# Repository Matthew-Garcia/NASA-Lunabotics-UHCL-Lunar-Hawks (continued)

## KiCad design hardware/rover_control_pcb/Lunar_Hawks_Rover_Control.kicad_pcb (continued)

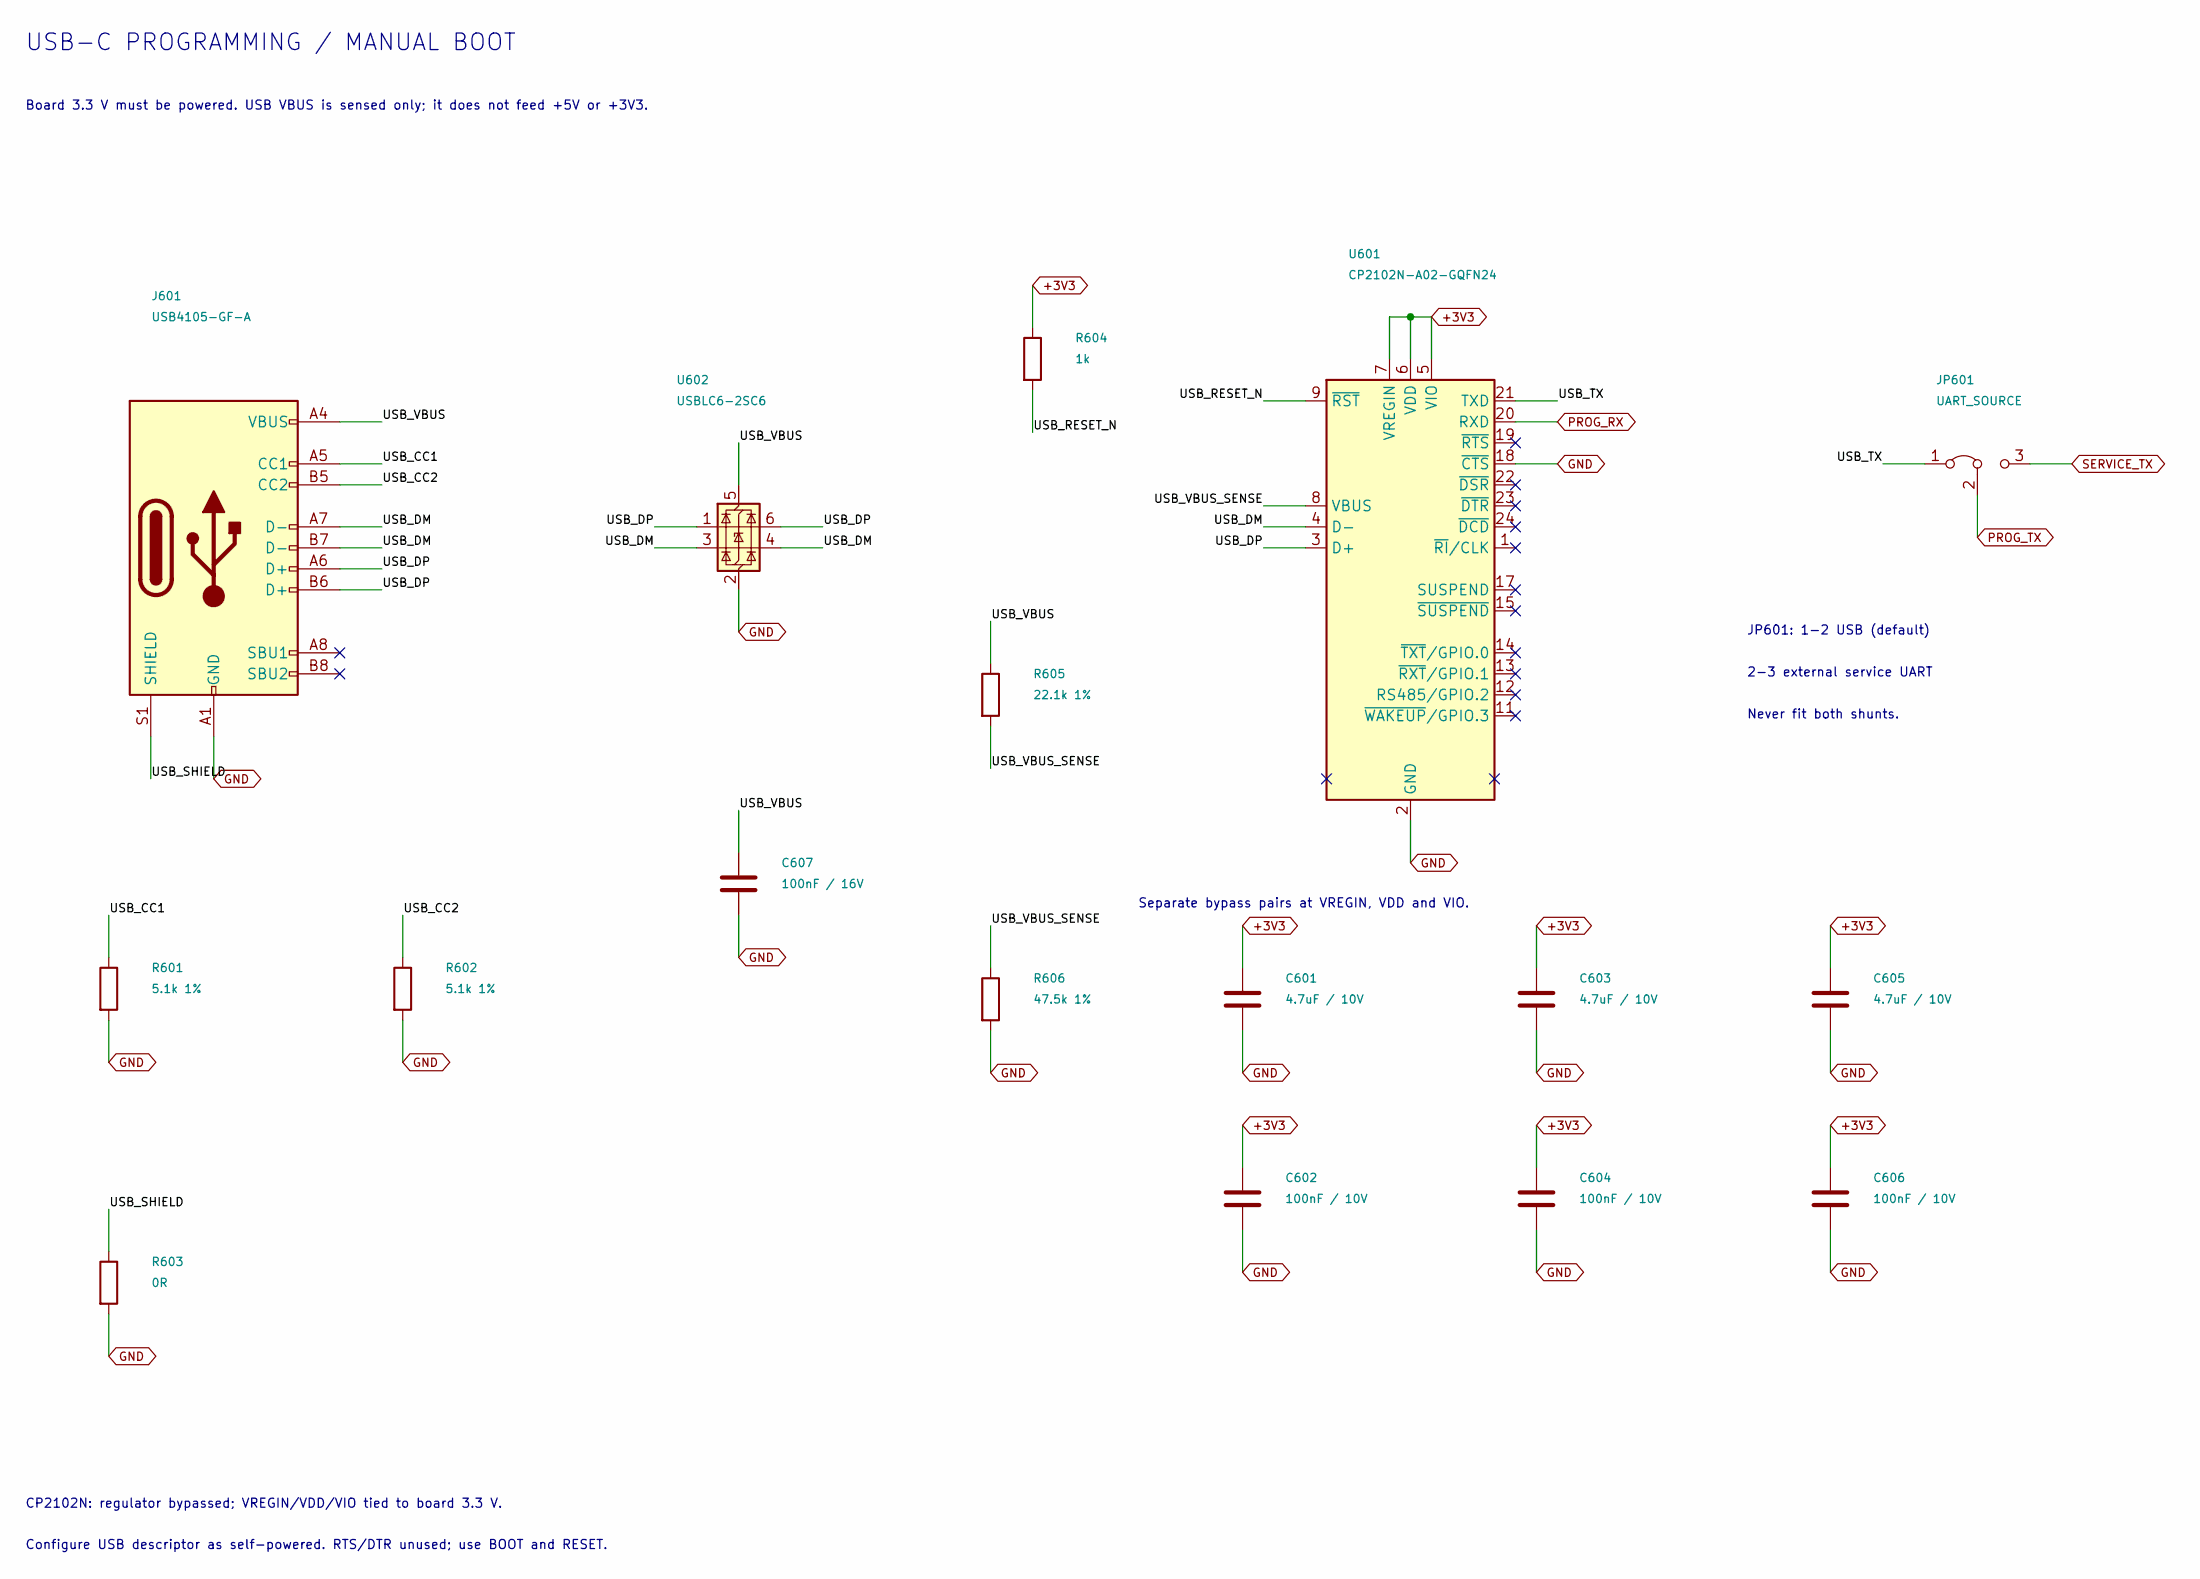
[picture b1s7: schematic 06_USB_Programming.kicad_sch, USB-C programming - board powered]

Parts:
C601, C603, C605: 4.7uF / 10V; C_0805_2012Metric
C602, C604, C606: 100nF / 10V; C_0603_1608Metric
C607: 100nF / 16V; C_0603_1608Metric
J601: USB4105-GF-A; USB_C_Receptacle_GCT_USB4105-xx-A_16P_TopMnt_Horizontal
JP601: UART_SOURCE; PinHeader_1x03_P2.54mm_Vertical
R601, R602: 5.1k 1%; R_0603_1608Metric
R603: 0R; R_0603_1608Metric
R604: 1k; R_0603_1608Metric
R605: 22.1k 1%; R_0603_1608Metric
R606: 47.5k 1%; R_0603_1608Metric
U601: CP2102N-A02-GQFN24; QFN-24-1EP_4x4mm_P0.5mm_EP2.6x2.6mm
U602: USBLC6-2SC6; SOT-23-6

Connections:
+3V3: C601.1, C602.1, C603.1, C604.1, C605.1, C606.1, R604.1, U601.5 (VIO), U601.6 (VDD), U601.7 (VREGIN); also elsewhere on the board
/USB-C programming - board powered/USB_CC1: J601.A5 (CC1), R601.1
/USB-C programming - board powered/USB_CC2: J601.B5 (CC2), R602.1
/USB-C programming - board powered/USB_DM: J601.A7 (D-), J601.B7 (D-), U601.4 (D-), U602.3 (I/O2), U602.4 (I/O2)
/USB-C programming - board powered/USB_DP: J601.A6 (D+), J601.B6 (D+), U601.3 (D+), U602.1 (I/O1), U602.6 (I/O1)
/USB-C programming - board powered/USB_RESET_N: R604.2, U601.9 (~RST)
/USB-C programming - board powered/USB_SHIELD: J601.S1 (SHIELD), R603.1
/USB-C programming - board powered/USB_TX: JP601.1 (A), U601.21 (TXD)
/USB-C programming - board powered/USB_VBUS: C607.1, J601.A4 (VBUS), J601.A9 (VBUS), J601.B4 (VBUS), J601.B9 (VBUS), R605.1, U602.5 (VBUS)
/USB-C programming - board powered/USB_VBUS_SENSE: R605.2, R606.1, U601.8 (VBUS)
GND: C601.2, C602.2, C603.2, C604.2, C605.2, C606.2, C607.2, J601.A1 (GND), J601.A12 (GND), J601.B1 (GND), J601.B12 (GND), R601.2, R602.2, R603.2, R606.2, U601.2 (GND), U601.18 (~CTS), U601.25 (GND), U602.2 (GND); also elsewhere on the board
PROG_RX: U601.20 (RXD); also elsewhere on the board
PROG_TX: JP601.2 (C); also elsewhere on the board
SERVICE_TX: JP601.3 (B); also elsewhere on the board

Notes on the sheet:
USB-C PROGRAMMING / MANUAL BOOT
Board 3.3 V must be powered. USB VBUS is sensed only; it does not feed +5V or +3V3.
JP601: 1-2 USB (default)
2-3 external service UART
Never fit both shunts.
Separate bypass pairs at VREGIN, VDD and VIO.
CP2102N: regulator bypassed; VREGIN/VDD/VIO tied to board 3.3 V.
Configure USB descriptor as self-powered. RTS/DTR unused; use BOOT and RESET.

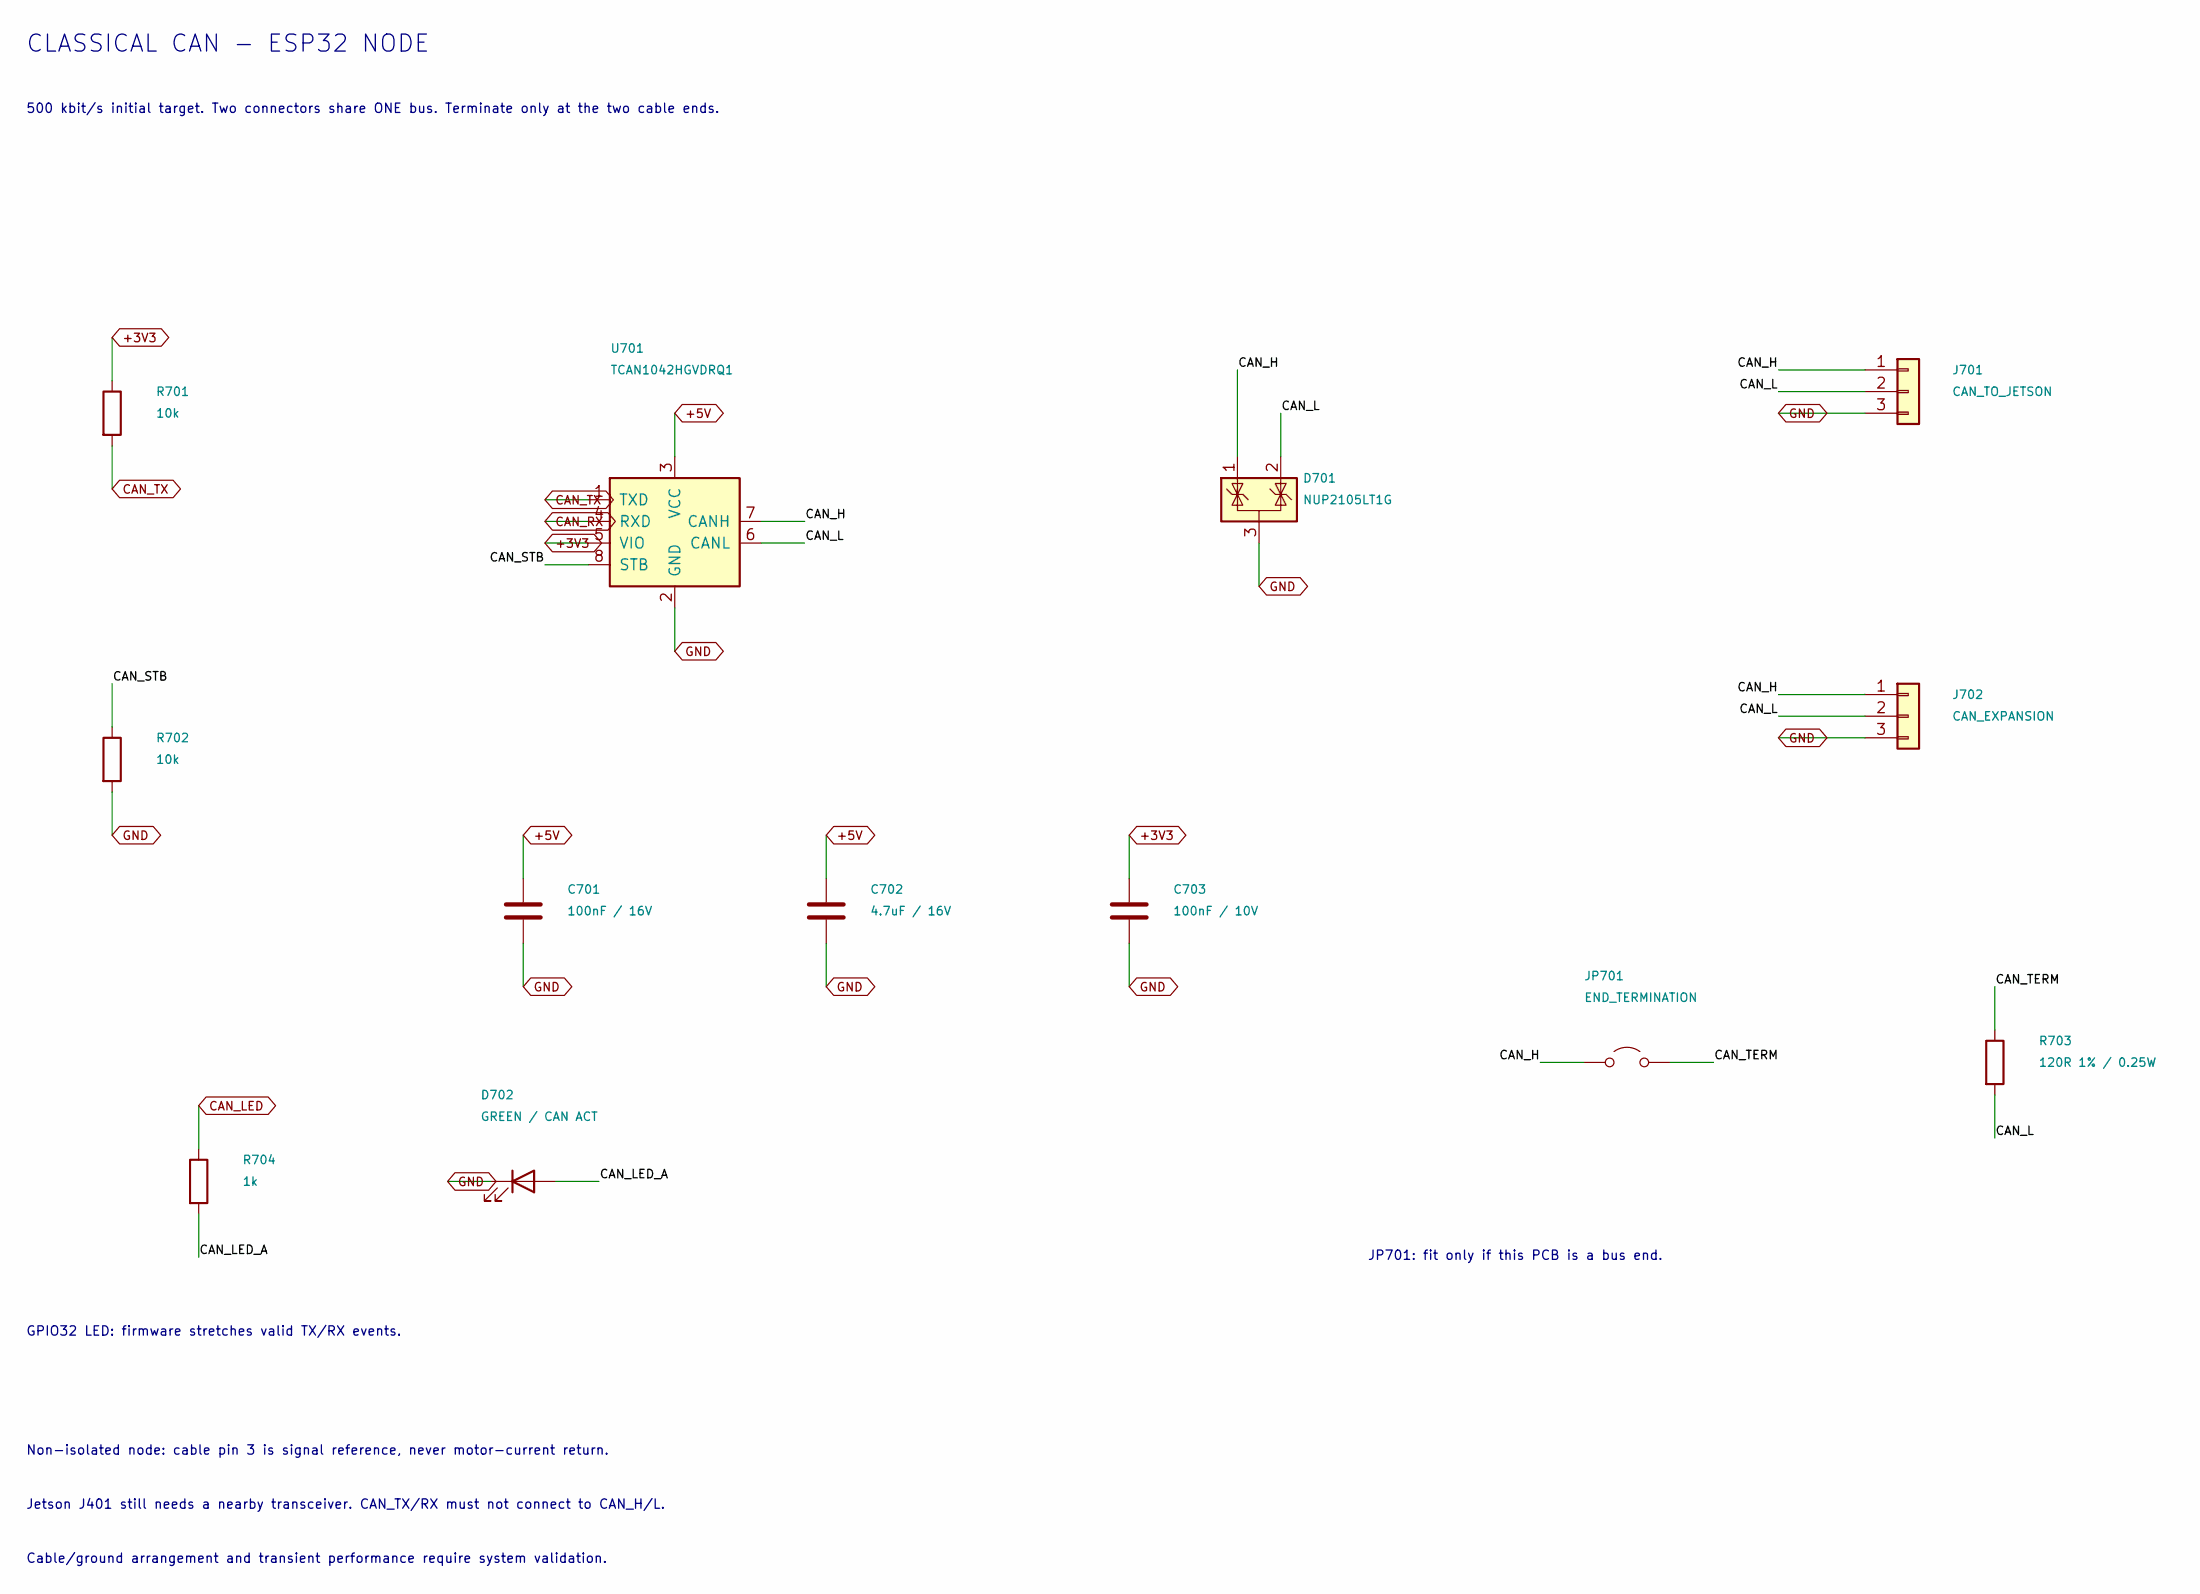
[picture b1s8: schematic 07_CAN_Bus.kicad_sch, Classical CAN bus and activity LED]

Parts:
C701: 100nF / 16V; C_0603_1608Metric
C702: 4.7uF / 16V; C_0805_2012Metric
C703: 100nF / 10V; C_0603_1608Metric
D701: NUP2105LT1G; SOT-23
D702: GREEN / CAN ACT; LED_0603_1608Metric
J701: CAN_TO_JETSON; Molex_Micro-Fit_3.0_43650-0300_1x03_P3.00mm_Horizontal
J702: CAN_EXPANSION; Molex_Micro-Fit_3.0_43650-0300_1x03_P3.00mm_Horizontal
JP701: END_TERMINATION; PinHeader_1x02_P2.54mm_Vertical
R701, R702: 10k; R_0603_1608Metric
R703: 120R 1% / 0.25W; R_1206_3216Metric
R704: 1k; R_0603_1608Metric
U701: TCAN1042HGVDRQ1; SOIC-8_3.9x4.9mm_P1.27mm

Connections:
+3V3: C703.1, R701.1, U701.5 (VIO); also elsewhere on the board
+5V: C701.1, C702.1, U701.3 (VCC); also elsewhere on the board
/Classical CAN bus and activity LED/CAN_H: D701.1 (K), J701.1, J702.1, JP701.1 (A), U701.7 (CANH)
/Classical CAN bus and activity LED/CAN_L: D701.2 (K), J701.2, J702.2, R703.2, U701.6 (CANL)
/Classical CAN bus and activity LED/CAN_LED_A: D702.2 (A), R704.2
/Classical CAN bus and activity LED/CAN_STB: R702.1, U701.8 (STB)
/Classical CAN bus and activity LED/CAN_TERM: JP701.2 (B), R703.1
CAN_LED: R704.1; also elsewhere on the board
CAN_RX: U701.4 (RXD); also elsewhere on the board
CAN_TX: R701.2, U701.1 (TXD); also elsewhere on the board
GND: C701.2, C702.2, C703.2, D701.3 (A), D702.1 (K), J701.3, J702.3, R702.2, U701.2 (GND); also elsewhere on the board

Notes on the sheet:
CLASSICAL CAN - ESP32 NODE
500 kbit/s initial target. Two connectors share ONE bus. Terminate only at the two cable ends.
JP701: fit only if this PCB is a bus end.
GPIO32 LED: firmware stretches valid TX/RX events.
Non-isolated node: cable pin 3 is signal reference, never motor-current return.
Jetson J401 still needs a nearby transceiver. CAN_TX/RX must not connect to CAN_H/L.
Cable/ground arrangement and transient performance require system validation.

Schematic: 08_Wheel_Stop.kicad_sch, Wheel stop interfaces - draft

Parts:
J801: WHEEL_1_STOP; PinHeader_1x03_P2.54mm_Vertical
J802: WHEEL_2_STOP; PinHeader_1x03_P2.54mm_Vertical
J803: WHEEL_3_STOP; PinHeader_1x03_P2.54mm_Vertical
J804: WHEEL_4_STOP; PinHeader_1x03_P2.54mm_Vertical
Q801, Q802, Q803, Q804, Q805: AO3400A; SOT-23
R801, R802, R803, R804: 680R 1%; R_0603_1608Metric
R805: 100k; R_0603_1608Metric
R811, R812, R813, R814: 47k 1%; R_0603_1608Metric
R821, R822, R823, R824: 0R DNP; R_0603_1608Metric; not fitted
U801, U802, U803, U804: LTV-817S-B; SMDIP-4_W9.53mm

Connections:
+5V: R801.1, R802.1, R803.1, R804.1; also elsewhere on the board
/Wheel stop interfaces/STOP_RELEASE_K: Q805.3 (D), U801.2, U802.2, U803.2, U804.2
/Wheel stop interfaces/W1_DRIVER_5V: J801.3, R811.1
/Wheel stop interfaces/W1_RELEASE_LED_A: R801.2, U801.1
/Wheel stop interfaces/W1_STOP_CONTACT: J801.2, R821.2
/Wheel stop interfaces/W1_STOP_DRAIN: Q801.3 (D), R821.1
/Wheel stop interfaces/W1_STOP_GATE: Q801.1 (G), R811.2, U801.4
/Wheel stop interfaces/W2_DRIVER_5V: J802.3, R812.1
/Wheel stop interfaces/W2_RELEASE_LED_A: R802.2, U802.1
/Wheel stop interfaces/W2_STOP_CONTACT: J802.2, R822.2
/Wheel stop interfaces/W2_STOP_DRAIN: Q802.3 (D), R822.1
/Wheel stop interfaces/W2_STOP_GATE: Q802.1 (G), R812.2, U802.4
/Wheel stop interfaces/W3_DRIVER_5V: J803.3, R813.1
/Wheel stop interfaces/W3_RELEASE_LED_A: R803.2, U803.1
/Wheel stop interfaces/W3_STOP_CONTACT: J803.2, R823.2
/Wheel stop interfaces/W3_STOP_DRAIN: Q803.3 (D), R823.1
/Wheel stop interfaces/W3_STOP_GATE: Q803.1 (G), R813.2, U803.4
/Wheel stop interfaces/W4_DRIVER_5V: J804.3, R814.1
/Wheel stop interfaces/W4_RELEASE_LED_A: R804.2, U804.1
/Wheel stop interfaces/W4_STOP_CONTACT: J804.2, R824.2
/Wheel stop interfaces/W4_STOP_DRAIN: Q804.3 (D), R824.1
/Wheel stop interfaces/W4_STOP_GATE: Q804.1 (G), R814.2, U804.4
GND: J801.1, J802.1, J803.1, J804.1, Q801.2 (S), Q802.2 (S), Q803.2 (S), Q804.2 (S), Q805.2 (S), R805.2, U801.3, U802.3, U803.3, U804.3; also elsewhere on the board
MOTION_ENABLED: Q805.1 (G), R805.1; also elsewhere on the board

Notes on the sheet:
WHEEL STOP / DRIVER-POWERED DEFAULT STOP REQUEST
Prototype only: populate STOP links after verifying actual ZS-X11H input behavior. This is not the battery-power E-stop.
Four separate driver 5 V inputs: NEVER join them to one another or the PCB 5 V rail. Signal grounds are shared; system is not isolated.
WHEEL 1: NO RELEASE LIGHT -> STOP SWITCH CLOSED
WHEEL 2: NO RELEASE LIGHT -> STOP SWITCH CLOSED
WHEEL 3: NO RELEASE LIGHT -> STOP SWITCH CLOSED
WHEEL 4: NO RELEASE LIGHT -> STOP SWITCH CLOSED
MOTION_ENABLED high lights all four optocouplers (~22 mA total from PCB 5 V) and pulls STOP gates low, opening the STOP switches.
J801-J804: 1 signal GND, 2 driver STOP terminal, 3 that driver's 5 V OUT. Not motor power. No BRAKE connection in this stage.

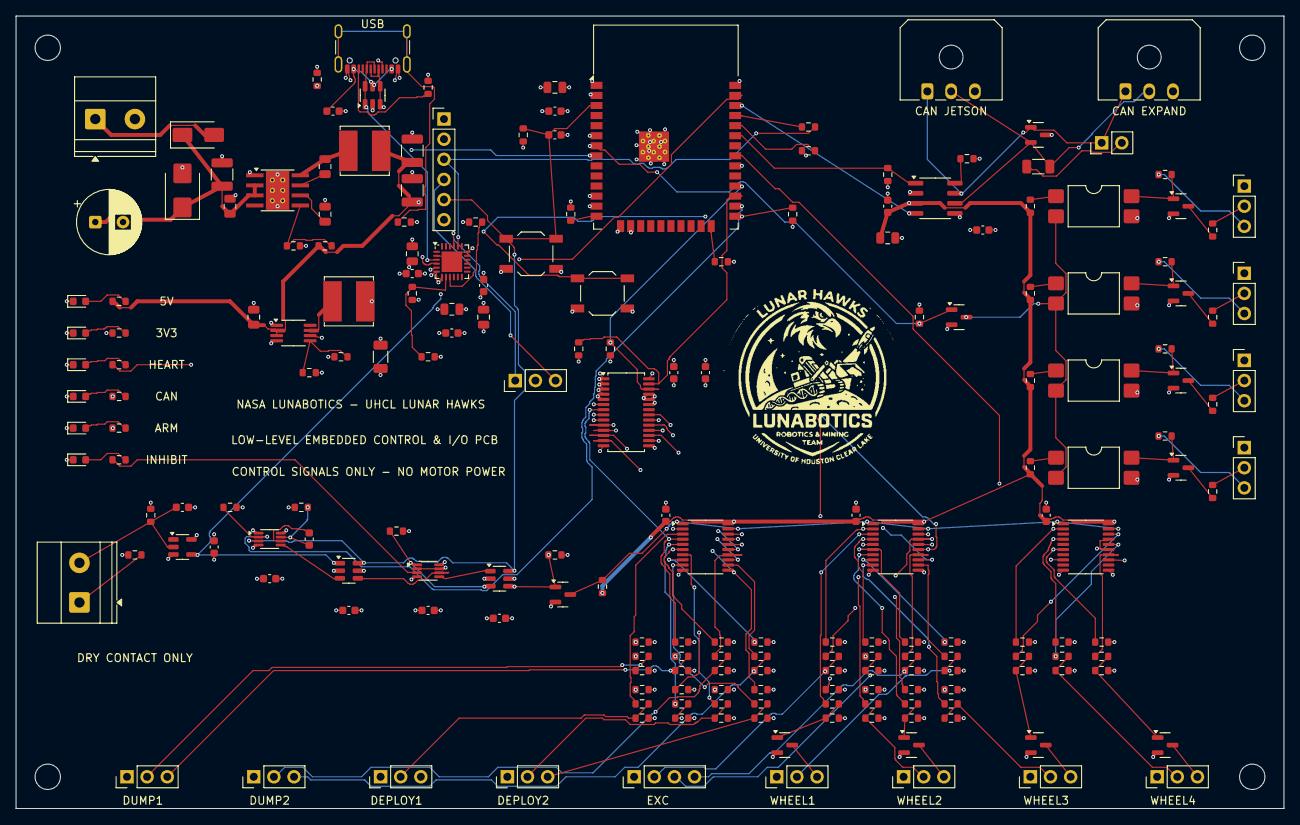
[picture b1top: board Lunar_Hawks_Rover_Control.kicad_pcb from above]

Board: 4 copper layers, 160.0 x 100.0 mm, 207 parts (1 on the bottom side), 140 nets.

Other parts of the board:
H1, H2, H3, H4: MountingHole_3.2mm_M3
LOGO1: UHCL_Lunar_Hawks_Logo
LOGO2: UHCL_Front_Logo_23mm

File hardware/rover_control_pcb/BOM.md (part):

# Lunar Hawks controller PCB — draft bill of materials

**Status: engineering draft; not released for procurement or assembly.**

Per board: **201 schematic components; 186 populated, 15 DNP.** Quantities do not include purchasing spares. Four board-only mounting holes are mechanical features, not electronic parts.

Generated from a fresh KiCad schematic netlist. References, values, and DNP status were checked against the current PCB. A specified part number is copied from the design, not a claim of stock availability or completed package validation.

## Assembly BOM

| Qty per board | Populate qty | References | Value / function | Specified part number | Footprint | Status |
| ---: | ---: | --- | --- | --- | --- | --- |
| 1 | 1 | C101 | 22uF / 63V | TBD | Capacitor_THT:CP_Radial_D8.0mm_P3.50mm | Populate; Exact ordering code not selected |
| 1 | 1 | C102 | 2.2uF / 100V X7R | TBD | Capacitor_SMD:C_1210_3225Metric | Populate; Exact ordering code not selected |
| 1 | 1 | C103 | 220nF / 100V X7R | TBD | Capacitor_SMD:C_0805_2012Metric | Populate; Exact ordering code not selected |
| 1 | 1 | C104 | 1uF / 10V | TBD | Capacitor_SMD:C_0805_2012Metric | Populate; Exact ordering code not selected |
| 1 | 1 | C105 | 100nF / 16V | TBD | Capacitor_SMD:C_0805_2012Metric | Populate; Exact ordering code not selected |
| 2 | 2 | C106, C107 | 22uF / 25V X7R | TBD | Capacitor_SMD:C_1210_3225Metric | Populate; Exact ordering code not selected |
| 1 | 1 | C108 | 10uF / 16V X7R | TBD | Capacitor_SMD:C_0805_2012Metric | Populate; Exact ordering code not selected |
| 1 | 1 | C109 | 22uF / 16V X7R | TBD | Capacitor_SMD:C_1206_3216Metric | Populate; Exact ordering code not selected |
| 1 | 1 | C201 | 10uF / 10V X7R | TBD | Capacitor_SMD:C_0805_2012Metric | Populate; Exact ordering code not selected |
| 1 | 1 | C202 | 100nF / 10V X7R | TBD | Capacitor_SMD:C_0603_1608Metric | Populate; Exact ordering code not selected |
| 1 | 1 | C203 | 1uF / 10V X7R | TBD | Capacitor_SMD:C_0603_1608Metric | Populate; Exact ordering code not selected |
| 1 | 1 | C301 | 10nF / 16V | TBD | Capacitor_SMD:C_0603_1608Metric | Populate; Exact ordering code not selected |
| 11 | 11 | C302, C304, C305, C306, C307, C401, C403, C404, C405, C607, C701 | 100nF / 16V | TBD | Capacitor_SMD:C_0603_1608Metric | Populate; Exact ordering code not selected |
| 1 | 1 | C303 | 1uF / 16V X7R | TBD | Capacitor_SMD:C_0603_1608Metric | Populate; Exact ordering code not selected |
| 1 | 1 | C402 | 4.7uF / 10V | TBD | Capacitor_SMD:C_0603_1608Metric | Populate; Exact ordering code not selected |
| 3 | 3 | C601, C603, C605 | 4.7uF / 10V | TBD | Capacitor_SMD:C_0805_2012Metric | Populate; Exact ordering code not selected |
| 4 | 4 | C602, C604, C606, C703 | 100nF / 10V | TBD | Capacitor_SMD:C_0603_1608Metric | Populate; Exact ordering code not selected |
| 1 | 1 | C702 | 4.7uF / 16V | TBD | Capacitor_SMD:C_0805_2012Metric | Populate; Exact ordering code not selected |
| 1 | 1 | D101 | STPS1H100A | STPS1H100A | Diode_SMD:D_SMA | Populate; Verify ordering code and package |
| 1 | 1 | D102 | SMBJ33A | SMBJ33A | Diode_SMD:D_SMB | Populate; Verify ordering code and package |
| 3 | 3 | D201, D202, D203 | GREEN | TBD | LED_SMD:LED_0603_1608Metric | Populate; Exact ordering code not selected |
| 1 | 1 | D301 | GREEN_COMMAND_ENABLE | TBD | LED_SMD:LED_0603_1608Metric | Populate; Exact ordering code not selected |
| 1 | 1 | D302 | RED_INHIBITED | TBD | LED_SMD:LED_0603_1608Metric | Populate; Exact ordering code not selected |
| 1 | 1 | D701 | NUP2105LT1G | NUP2105LT1G | Package_TO_SOT_SMD:SOT-23 | Populate; Verify ordering code and package |
| 1 | 1 | D702 | GREEN / CAN ACT | TBD | LED_SMD:LED_0603_1608Metric | Populate; Exact ordering code not selected |
| 1 | 1 | J101 | FUSED_LOGIC_INPUT | TBD | TerminalBlock_Phoenix:TerminalBlock_Phoenix_MKDS-1,5-2_1x02_P5.00mm_Horizontal | Populate; Exact ordering code not selected |
| 1 | 1 | J201 | SERVICE_UART_3V3 | TBD | Connector_PinHeader_2.54mm:PinHeader_1x06_P2.54mm_Vertical | Populate; Exact ordering code not selected |
| 1 | 1 | J301 | SAFETY_AUX_DRY_CONTACT | TBD | TerminalBlock_Phoenix:TerminalBlock_Phoenix_MKDS-1,5-2_1x02_P5.00mm_Horizontal | Populate; Exact ordering code not selected |
| 1 | 1 | J401 | DUMP_1 | TBD | Connector_PinHeader_2.54mm:PinHeader_1x03_P2.54mm_Vertical | Populate; Exact ordering code not selected |
| 1 | 1 | J402 | DUMP_2 | TBD | Connector_PinHeader_2.54mm:PinHeader_1x03_P2.54mm_Vertical | Populate; Exact ordering code not selected |
| 1 | 1 | J403 | DEPLOY_1 | TBD | Connector_PinHeader_2.54mm:PinHeader_1x03_P2.54mm_Vertical | Populate; Exact ordering code not selected |
| 1 | 1 | J404 | DEPLOY_2 | TBD | Connector_PinHeader_2.54mm:PinHeader_1x03_P2.54mm_Vertical | Populate; Exact ordering code not selected |
| 1 | 1 | J405 | EXCAVATOR | TBD | Connector_PinHeader_2.54mm:PinHeader_1x04_P2.54mm_Vertical | Populate; Exact ordering code not selected |
| 1 | 1 | J406 | WHEEL_1 | TBD | Connector_PinHeader_2.54mm:PinHeader_1x03_P2.54mm_Vertical | Populate; Exact ordering code not selected |
| 1 | 1 | J407 | WHEEL_2 | TBD | Connector_PinHeader_2.54mm:PinHeader_1x03_P2.54mm_Vertical | Populate; Exact ordering code not selected |
| 1 | 1 | J408 | WHEEL_3 | TBD | Connector_PinHeader_2.54mm:PinHeader_1x03_P2.54mm_Vertical | Populate; Exact ordering code not selected |
| 1 | 1 | J409 | WHEEL_4 | TBD | Connector_PinHeader_2.54mm:PinHeader_1x03_P2.54mm_Vertical | Populate; Exact ordering code not selected |
| 1 | 1 | J601 | USB4105-GF-A | USB4105-GF-A | Connector_USB:USB_C_Receptacle_GCT_USB4105-xx-A_16P_TopMnt_Horizontal | Populate; Verify ordering code and package |
| 1 | 1 | J701 | CAN_TO_JETSON | TBD | Connector_Molex:Molex_Micro-Fit_3.0_43650-0300_1x03_P3.00mm_Horizontal | Populate; Exact ordering code not selected |
| 1 | 1 | J702 | CAN_EXPANSION | TBD | Connector_Molex:Molex_Micro-Fit_3.0_43650-0300_1x03_P3.00mm_Horizontal | Populate; Exact ordering code not selected |
| 1 | 1 | J801 | WHEEL_1_STOP | TBD | Connector_PinHeader_2.54mm:PinHeader_1x03_P2.54mm_Vertical | Populate; Exact ordering code not selected |
| 1 | 1 | J802 | WHEEL_2_STOP | TBD | Connector_PinHeader_2.54mm:PinHeader_1x03_P2.54mm_Vertical | Populate; Exact ordering code not selected |
| 1 | 1 | J803 | WHEEL_3_STOP | TBD | Connector_PinHeader_2.54mm:PinHeader_1x03_P2.54mm_Vertical | Populate; Exact ordering code not selected |
| 1 | 1 | J804 | WHEEL_4_STOP | TBD | Connector_PinHeader_2.54mm:PinHeader_1x03_P2.54mm_Vertical | Populate; Exact ordering code not selected |
| 1 | 1 | JP601 | UART_SOURCE | TBD | Connector_PinHeader_2.54mm:PinHeader_1x03_P2.54mm_Vertical | Populate; Exact ordering code not selected |
| 1 | 1 | JP701 | END_TERMINATION | TBD | Connector_PinHeader_2.54mm:PinHeader_1x02_P2.54mm_Vertical | Populate; Exact ordering code not selected |
| 1 | 1 | L101 | 22uH / SRN6045TA-220M | SRN6045TA-220M | Inductor_SMD:L_Bourns_SRN6045TA | Populate; Verify ordering code and package |
| 1 | 1 | L102 | 3.3uH / SRN6045TA-3R3Y | SRN6045TA-3R3Y | Inductor_SMD:L_Bourns_SRN6045TA | Populate; Verify ordering code and package |
| 10 | 10 | Q301, Q401, Q402, Q403, Q404, Q801, Q802, Q803, Q804, Q805 | AO3400A | AO3400A | Package_TO_SOT_SMD:SOT-23 | Populate; Verify ordering code and package |
| 2 | 2 | R101, R104 | 100k 1% | TBD | Resistor_SMD:R_0603_1608Metric | Populate; Exact ordering code not selected |
| 1 | 1 | R102 | 24.9k 1% | TBD | Resistor_SMD:R_0603_1608Metric | Populate; Exact ordering code not selected |
| 1 | 1 | R103 | 312k 1% | TBD | Resistor_SMD:R_0603_1608Metric | Populate; Exact ordering code not selected |
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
